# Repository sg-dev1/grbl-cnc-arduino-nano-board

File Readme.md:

# Overview

This repository contains the schematics/ pcb layout for a GRBL control board.

The PCB layout is fit onto a 7x5 cm pcb.

# Description

Due to custom pin assignments a custom GRBL version needs to be used [1].

Components required:
 * 1 7x5 cm pcb
 * 1 Arduino Nano
 * 3 stepper drivers (A4988 or similar)
 * 3 100 uf capacitators used between VMOT and GNDMOT
 * 3 0.1 uf capacitators for endstops/ probe connector
 * Female headers to attach Arduino Nano and stepper drivers
 * 3 JST XH connectors for endstops and probe connector
 * Additional extension header to mount Arduino Nano a bit higher to have space for connectors (I soldered together male and female pin headers for that)
 * Screw terminal soldered onto some cables for power connector
 
 A 3d printable case can be found on thingiverse: https://www.thingiverse.com/thing:4709614

[1] https://github.com/sg-dev1/grbl

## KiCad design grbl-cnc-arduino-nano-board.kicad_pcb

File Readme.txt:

This repository contains the schematics/ pcb layout for a GRBL control board.
The PCB layout is fit onto a 7x5 cm pcb.

Due to custom pin assignments a custom GRBL version needs to be used [1].

Components required:
 * 1 7x5 cm pcb
 * 1 Arduino Nano
 * 3 stepper drivers (A4988 or similar)
 * 3 100 uf capacitators used between VMOT and GNDMOT
 * 3 0.1 uf capacitators for endstops/ probe connector
 * Female headers to attach Arduino Nano and stepper drivers
 * 3 JST XH connectors for endstops and probe connector
 * Additional extension header to mount Arduino Nano a bit higher to have space for connectors (I soldered together male and female pin headers for that)
 * Screw terminal soldered onto some cables for power connector

[1] https://github.com/sg-dev1/grbl

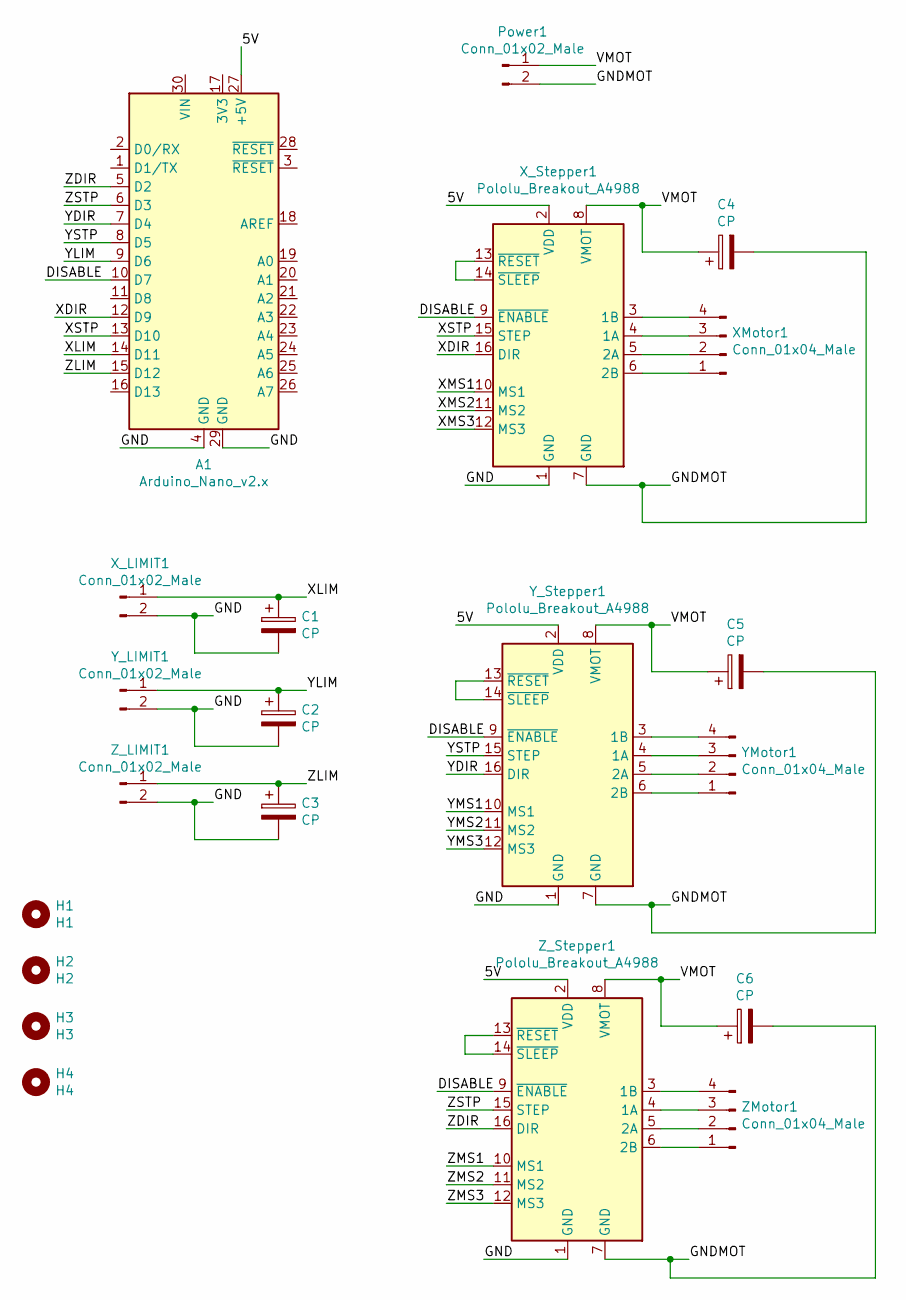
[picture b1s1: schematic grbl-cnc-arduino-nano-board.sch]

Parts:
A1: Arduino_Nano_v2.x; Arduino_Nano
C1, C2, C3, C4, C5, C6: CP; Capacitator_Radial_D5.0mm_P2.50mm
H1: H1; MountingHole_3.2mm_M3
H2: H2; MountingHole_3.2mm_M3
H3: H3; MountingHole_3.2mm_M3
H4: H4; MountingHole_3.2mm_M3
Power1: Conn_01x02_Male; PinHeader_1x02_P2.54mm_Vertical
XMotor1: Conn_01x04_Male; PinHeader_1x04_P2.54mm_Vertical
X_LIMIT1: Conn_01x02_Male; JST_XH_B2B-XH-A_1x02_P2.50mm_Vertical
X_Stepper1: Pololu_Breakout_A4988; Pololu_Breakout-16_15.2x20.3mm_custom
YMotor1: Conn_01x04_Male; PinHeader_1x04_P2.54mm_Vertical
Y_LIMIT1: Conn_01x02_Male; JST_XH_B2B-XH-A_1x02_P2.50mm_Vertical
Y_Stepper1: Pololu_Breakout_A4988; Pololu_Breakout-16_15.2x20.3mm_custom
ZMotor1: Conn_01x04_Male; PinHeader_1x04_P2.54mm_Vertical
Z_LIMIT1: Conn_01x02_Male; JST_XH_B2B-XH-A_1x02_P2.50mm_Vertical
Z_Stepper1: Pololu_Breakout_A4988; Pololu_Breakout-16_15.2x20.3mm_custom

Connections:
/5V: A1.27 (+5V), X_Stepper1.2 (VDD), Y_Stepper1.2 (VDD), Z_Stepper1.2 (VDD)
/DISABLE: A1.10 (D7), X_Stepper1.9 (~ENABLE), Y_Stepper1.9 (~ENABLE), Z_Stepper1.9 (~ENABLE)
/GND: A1.4 (GND), A1.29 (GND), C1.2, C2.2, C3.2, X_LIMIT1.2, X_Stepper1.1 (GND), Y_LIMIT1.2, Y_Stepper1.1 (GND), Z_LIMIT1.2, Z_Stepper1.1 (GND)
/GNDMOT: C4.2, C5.2, C6.2, Power1.2, X_Stepper1.7 (GND), Y_Stepper1.7 (GND), Z_Stepper1.7 (GND)
/VMOT: C4.1, C5.1, C6.1, Power1.1, X_Stepper1.8 (VMOT), Y_Stepper1.8 (VMOT), Z_Stepper1.8 (VMOT)
/XDIR: A1.12 (D9), X_Stepper1.16 (DIR)
/XLIM: A1.14 (D11), C1.1, X_LIMIT1.1
/XMS1: X_Stepper1.10 (MS1)
/XMS2: X_Stepper1.11 (MS2)
/XMS3: X_Stepper1.12 (MS3)
/XSTP: A1.13 (D10), X_Stepper1.15 (STEP)
/YDIR: A1.7 (D4), Y_Stepper1.16 (DIR)
/YLIM: A1.9 (D6), C2.1, Y_LIMIT1.1
/YMS1: Y_Stepper1.10 (MS1)
/YMS2: Y_Stepper1.11 (MS2)
/YMS3: Y_Stepper1.12 (MS3)
/YSTP: A1.8 (D5), Y_Stepper1.15 (STEP)
/ZDIR: A1.5 (D2), Z_Stepper1.16 (DIR)
/ZLIM: A1.15 (D12), C3.1, Z_LIMIT1.1
/ZMS1: Z_Stepper1.10 (MS1)
/ZMS2: Z_Stepper1.11 (MS2)
/ZMS3: Z_Stepper1.12 (MS3)
/ZSTP: A1.6 (D3), Z_Stepper1.15 (STEP)
unnamed: XMotor1.1, X_Stepper1.6 (2B)
unnamed: XMotor1.2, X_Stepper1.5 (2A)
unnamed: XMotor1.3, X_Stepper1.4 (1A)
unnamed: XMotor1.4, X_Stepper1.3 (1B)
unnamed: X_Stepper1.13 (~RESET), X_Stepper1.14 (~SLEEP)
unnamed: YMotor1.1, Y_Stepper1.6 (2B)
unnamed: YMotor1.2, Y_Stepper1.5 (2A)
unnamed: YMotor1.3, Y_Stepper1.4 (1A)
unnamed: YMotor1.4, Y_Stepper1.3 (1B)
unnamed: Y_Stepper1.13 (~RESET), Y_Stepper1.14 (~SLEEP)
unnamed: ZMotor1.1, Z_Stepper1.6 (2B)
unnamed: ZMotor1.2, Z_Stepper1.5 (2A)
unnamed: ZMotor1.3, Z_Stepper1.4 (1A)
unnamed: ZMotor1.4, Z_Stepper1.3 (1B)
unnamed: Z_Stepper1.13 (~RESET), Z_Stepper1.14 (~SLEEP)

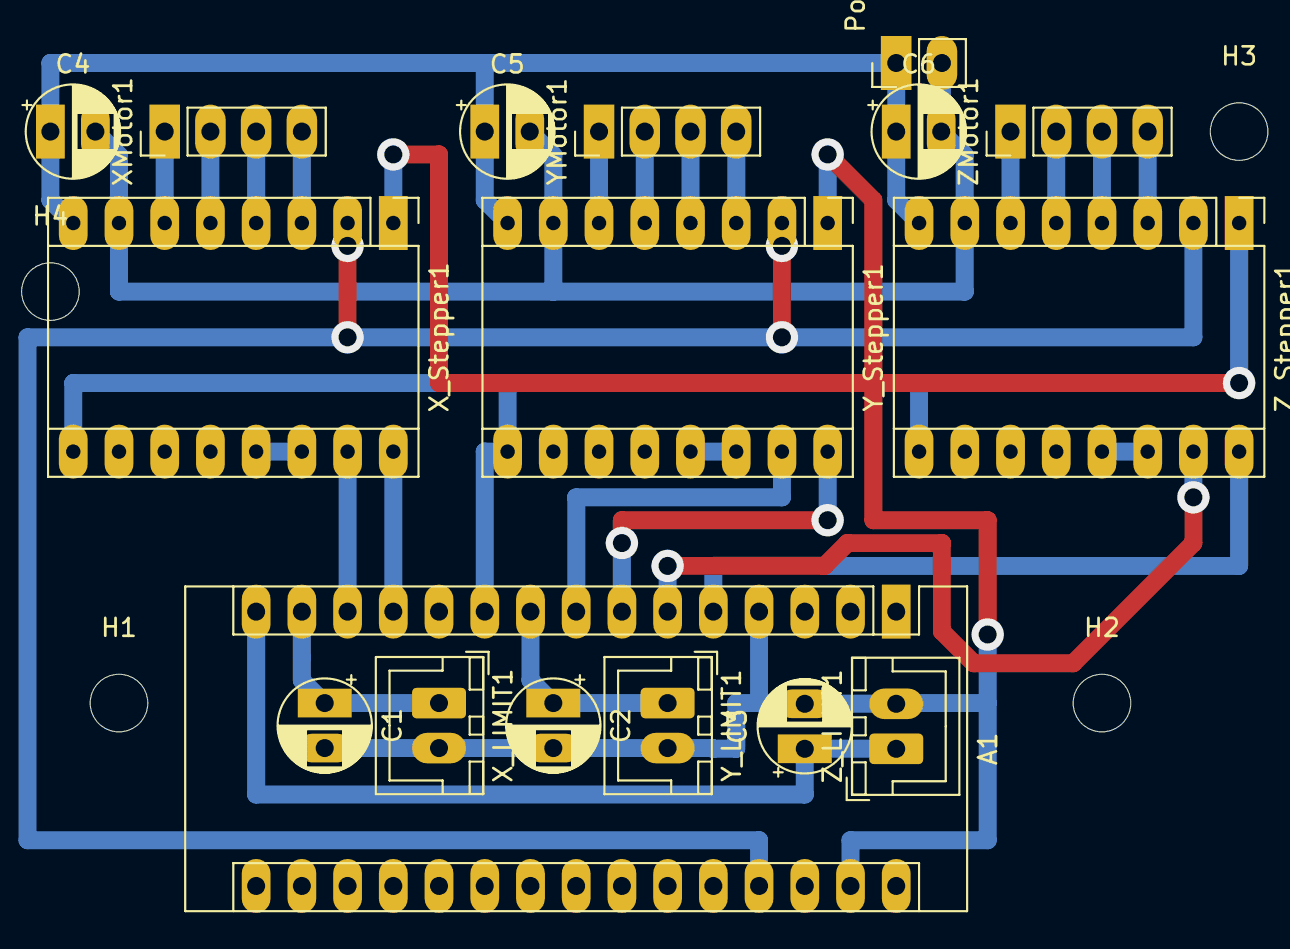
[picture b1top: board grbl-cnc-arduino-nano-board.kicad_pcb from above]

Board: 2 copper layers, 21 parts (0 on the bottom side), 29 nets.

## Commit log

2021-01-04 added files
2021-01-04 Rename Readme.txt to Readme.md
